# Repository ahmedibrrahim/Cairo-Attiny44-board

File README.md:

# Cairo-Attiny44-board
Cairo Attiny44 board PCB Eagle Project

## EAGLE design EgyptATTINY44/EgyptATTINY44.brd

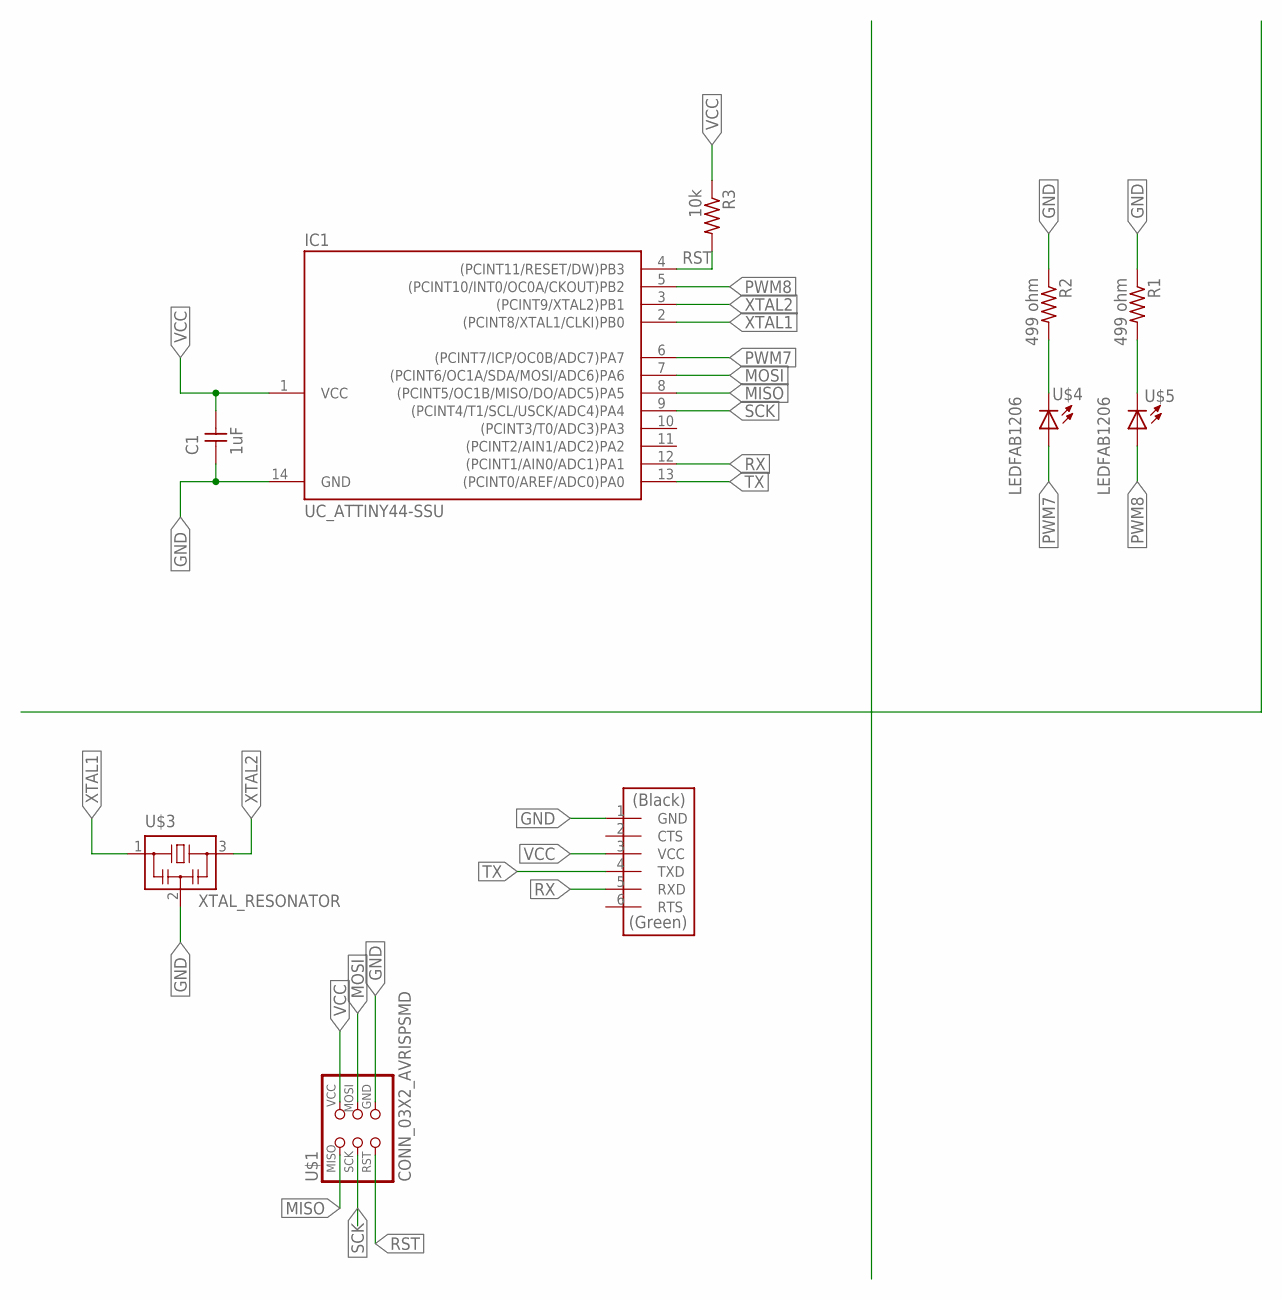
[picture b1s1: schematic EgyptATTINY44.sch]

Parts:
C1: 1uF; C1206FAB
IC1: UC_ATTINY44-SSU; SOIC14
R1, R2: 499 ohm; R1206FAB
R3: 10k; R1206FAB
U$1: CONN_03X2_AVRISPSMD; 2X03SMD
U$2: CONN_06_FTDI-SMD-HEADER; 1X06SMD
U$3: XTAL_RESONATOR; EFOBM
U$4, U$5: LEDFAB1206; LED1206FAB

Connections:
GND: C1.1, IC1.14 (GND), R1.1, R2.1, U$1.6 (GND), U$2.1 (GND), U$3.2
MISO: IC1.8 ((PCINT5/OC1B/MISO/DO/ADC5)PA5), U$1.1 (MISO)
MOSI: IC1.7 ((PCINT6/OC1A/SDA/MOSI/ADC6)PA6), U$1.4 (MOSI)
unnamed: R2.2, U$4.2 (C)
unnamed: R1.2, U$5.2 (C)
PWM7: IC1.6 ((PCINT7/ICP/OC0B/ADC7)PA7), U$4.1 (A)
PWM8: IC1.5 ((PCINT10/INT0/OC0A/CKOUT)PB2), U$5.1 (A)
RST: IC1.4 ((PCINT11/RESET/DW)PB3), R3.2, U$1.5 (RST)
RX: IC1.12 ((PCINT1/AIN0/ADC1)PA1), U$2.5 (RXD)
SCK: IC1.9 ((PCINT4/T1/SCL/USCK/ADC4)PA4), U$1.3 (SCK)
TX: IC1.13 ((PCINT0/AREF/ADC0)PA0), U$2.4 (TXD)
VCC: C1.2, IC1.1 (VCC), R3.1, U$1.2 (VCC), U$2.3 (VCC)
XTAL1: IC1.2 ((PCINT8/XTAL1/CLKI)PB0), U$3.1
XTAL2: IC1.3 ((PCINT9/XTAL2)PB1), U$3.3

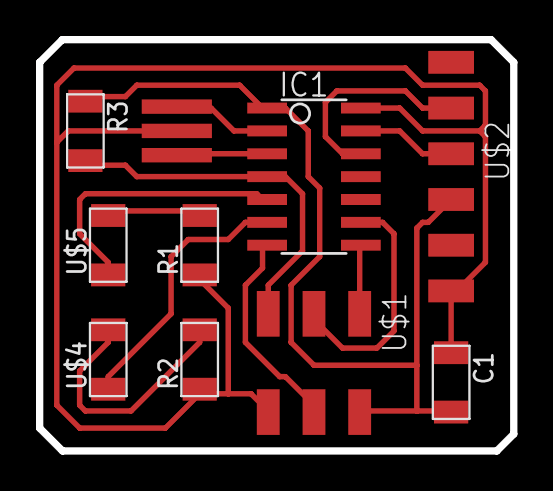
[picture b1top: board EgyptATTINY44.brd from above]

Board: 2 copper layers, 26.3 x 22.9 mm, 10 parts (0 on the bottom side), 14 nets.

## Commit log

2020-02-28 Initial Upload

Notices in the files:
parts and their libraries:
SparkFun-Aesthetics: Licensing: Creative Commons ShareAlike 4.0 International - https://creativecommons.org/licenses/by-sa/4.0
